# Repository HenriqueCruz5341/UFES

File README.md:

# UFES
Repositório para adicionar os exercícios e projetos que realizo durante minhas matérias que envolvem programação do curso de Engenharia de Computação, na UFES Campus Goiabeiras.

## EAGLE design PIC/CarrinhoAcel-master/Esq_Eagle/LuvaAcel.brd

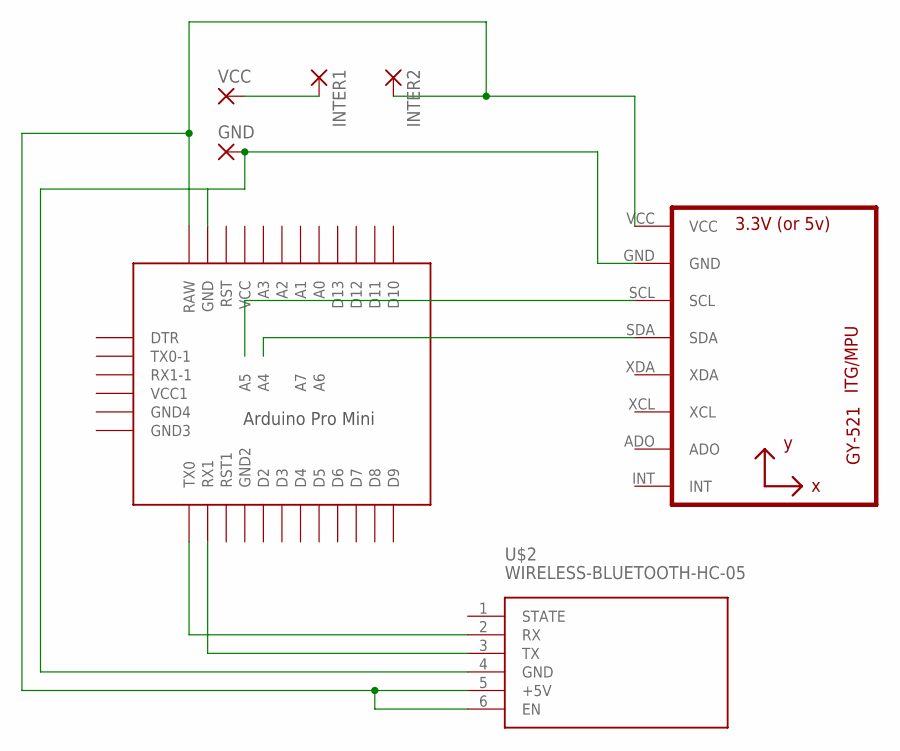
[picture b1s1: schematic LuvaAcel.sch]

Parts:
GND: 3,17/1,1
INTER1, INTER2: 3,17/1,1
U1: GY-521MPU6050; GY-521
U$1: PRO-MINI-2
U$2: WIRELESS-BLUETOOTH-HC-05
VCC: 3,17/1,1

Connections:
unnamed: U1.SCL, U$1.A5
unnamed: U1.SDA, U$1.A4
unnamed: GND.1, U1.GND, U$1.GND, U$2.4 (GND)
unnamed: U$1.TX0, U$2.2 (RX)
unnamed: U$1.RX1, U$2.3 (TX)
unnamed: INTER2.1, U1.VCC, U$1.RAW, U$2.5 (+5V), U$2.6 (EN)
unnamed: INTER1.1, VCC.1

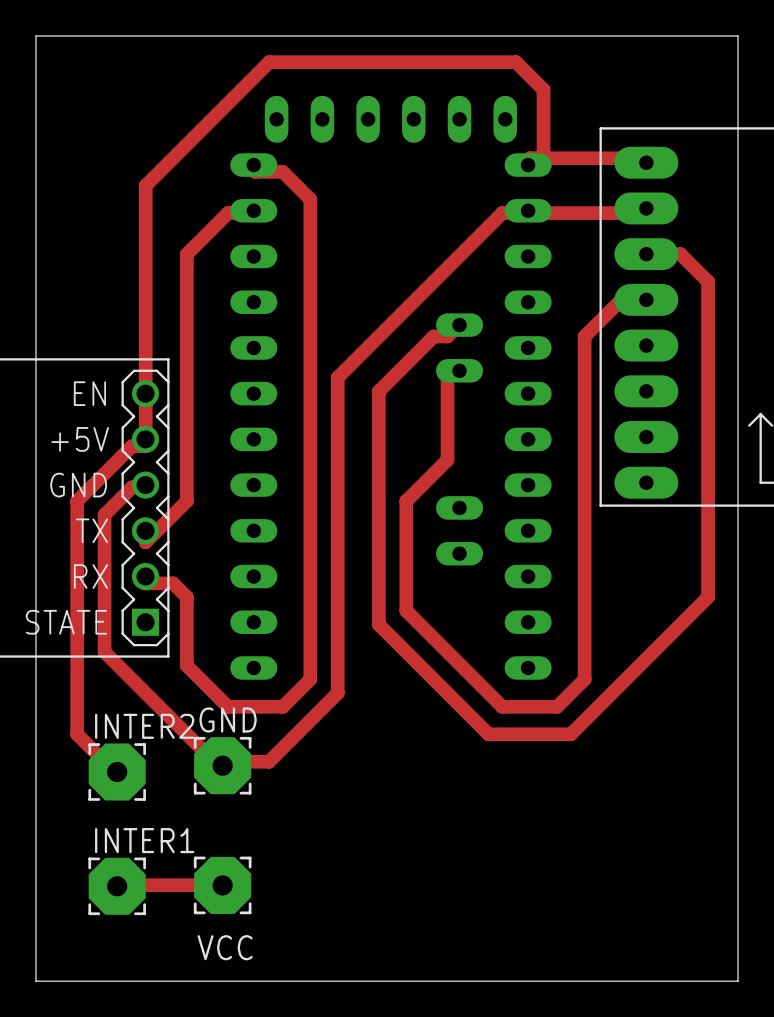
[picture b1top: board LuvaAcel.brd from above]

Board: 2 copper layers, 39.0 x 52.5 mm, 7 parts (0 on the bottom side), 7 nets.

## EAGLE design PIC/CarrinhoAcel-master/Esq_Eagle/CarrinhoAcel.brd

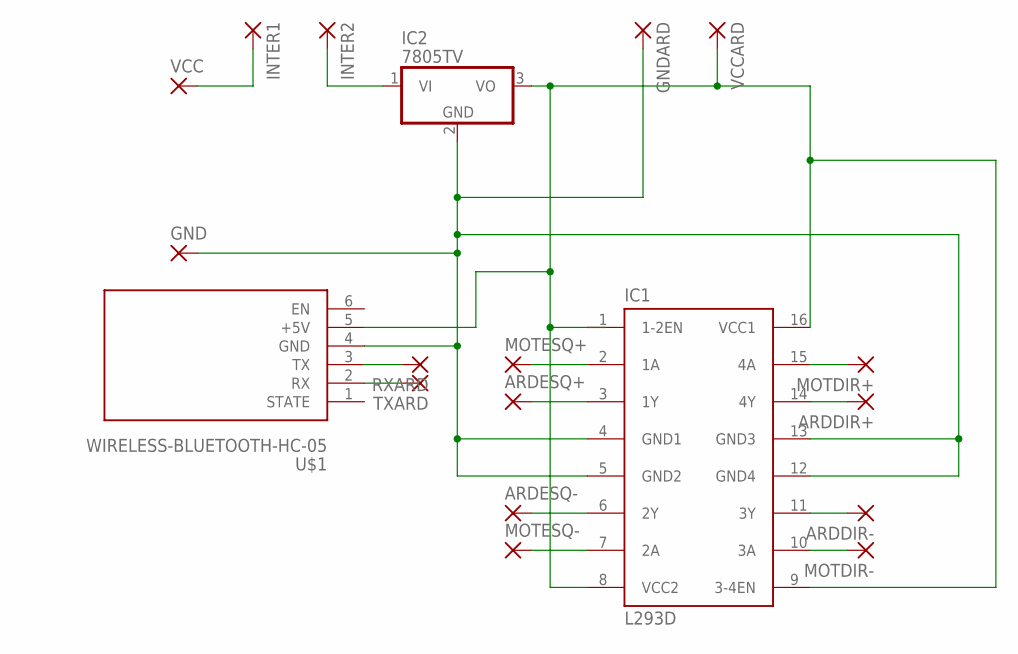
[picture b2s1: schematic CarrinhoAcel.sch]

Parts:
ARDDIR+: 2,15/1,0
ARDDIR-: 2,15/1,0
ARDESQ+: 2,15/1,0
ARDESQ-: 2,15/1,0
GND: 2,15/1,0
GNDARD: 2,15/1,0
IC1: L293D; DIL16
IC2: 7805TV; TO220V
INTER1, INTER2: 2,15/1,0
MOTDIR+: 2,15/1,0
MOTDIR-: 2,15/1,0
MOTESQ+: 2,15/1,0
MOTESQ-: 2,15/1,0
RXARD: 2,15/1,0
TXARD: 2,15/1,0
U$1: WIRELESS-BLUETOOTH-HC-05
VCC: 2,15/1,0
VCCARD: 2,15/1,0

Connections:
unnamed: INTER1.1, VCC.1
unnamed: GND.1, GNDARD.1, IC1.4 (GND1), IC1.5 (GND2), IC1.12 (GND4), IC1.13 (GND3), IC2.2 (GND), U$1.4 (GND)
unnamed: IC1.2 (1A), MOTESQ+.1
unnamed: ARDESQ+.1, IC1.3 (1Y)
unnamed: ARDESQ-.1, IC1.6 (2Y)
unnamed: IC1.7 (2A), MOTESQ-.1
unnamed: IC1.1 (1-2EN), IC1.8 (VCC2), IC1.9 (3-4EN), IC1.16 (VCC1), IC2.3 (VO), U$1.5 (+5V), VCCARD.1
unnamed: IC1.10 (3A), MOTDIR-.1
unnamed: ARDDIR-.1, IC1.11 (3Y)
unnamed: ARDDIR+.1, IC1.14 (4Y)
unnamed: IC1.15 (4A), MOTDIR+.1
unnamed: RXARD.1, U$1.3 (TX)
unnamed: IC2.1 (VI), INTER2.1
unnamed: TXARD.1, U$1.2 (RX)

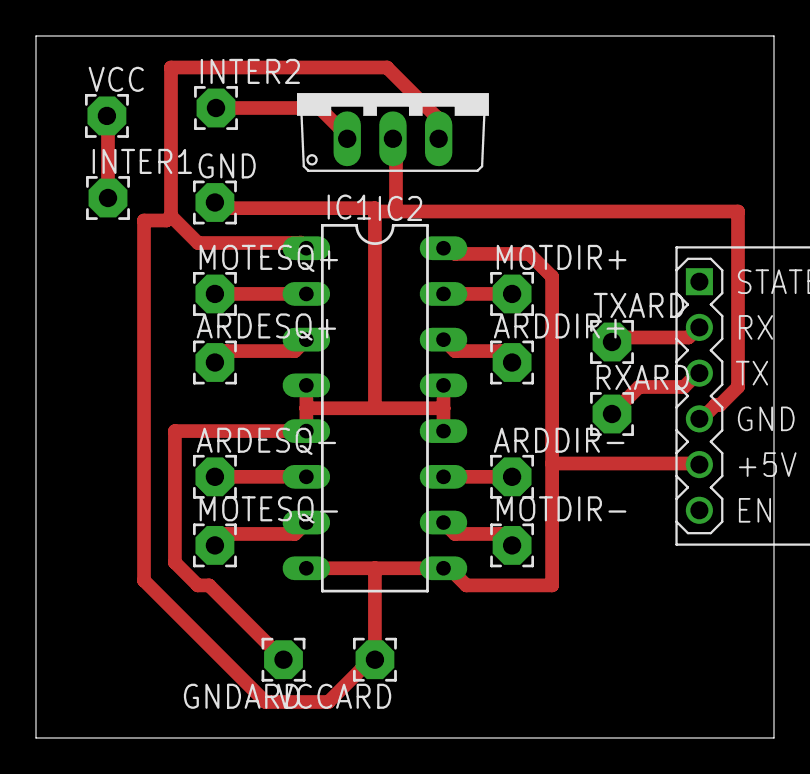
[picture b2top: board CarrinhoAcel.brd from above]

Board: 2 copper layers, 41.0 x 39.0 mm, 19 parts (0 on the bottom side), 14 nets.

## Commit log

2019-09-17 Adicionando o .gitignore para PDF
2019-09-17 Adicionando exercicios de TEP_I e PROG_II
2019-09-17 Removi o arquivo Jogo.zip da pasta Prog_II
2019-09-26 Adicionando mais exercicios e PIC
2019-09-26 Adicionando mais exercicios
2019-10-03 Adicionando BigInt_06
2019-10-04 Adicionando exercicio BigInt_05
2019-10-09 Adicionando exercicio do acelerometro completo
2019-10-17 Adicionando exercicio e Ponto
2019-10-22 Adicionando TAD circulo
2019-10-29 Atualizando o projeto Ponto
2019-10-29 Exemplo de makefile e TAD matriz
2019-10-31 Update 31/10
2019-10-31 comecando trabalho
2019-11-05 Nao alterei nada
2019-11-06 modificacoes no trabalho0
2019-11-07 alteracoes no trabalho
2019-11-07 mudancas trabalho ufes
2019-11-07 Concertando
2019-11-07 funcionando algumas edicoes
2019-11-11 atualizacao trabalho
2019-11-12 Comecando a mexer com usuarios
2019-11-13 melhorando usuarios
2019-11-14 melhorando trabalho
2019-11-17 Comecando a implementar playlists
2019-11-19 Terminei playlists
2019-11-19 Comecando a implementar sistema
2019-11-20 avancei na parte de usuarios publicos e admin
2019-11-21 Terminei o bruto
2019-11-21 Concertando erros
2019-11-21 Aparentemente, ta pronto
2019-11-26 Atualiacoes
2019-11-26 Comecando a documentacao
2019-11-27 continuando a documentacao
2019-11-28 Atualizando
2019-11-28 Terminei de comentar a main
2019-11-29 terminando comentarios da main
2019-12-01 Terminei a documentacao
2019-12-07 Colocando o PDF
2019-12-10 colocando o programa em estagio padrao
2019-12-11 colocando arquivos do curso de JS
2019-12-18 Adicionando cursoJS
2020-01-06 criando singlePage
2020-01-07 adicionando um Exemplo de integração entre React e Bootstrap
2020-02-05 Curso Omnistack
2020-02-26 Melhorando teste da JACEE
2020-02-27 Melhorando site JACEE
2020-03-15 adicionando ED1
2020-03-18 Adicionando exercicio da aula2 de ED1
2020-04-09 Adicionando exercicios da Aula3 de ED1
2020-04-22 Adicionando a pasta web do PET para backup
2020-04-22 Bump minimist from 1.2.0 to 1.2.5 in /web/jacee/backend
    Bumps [minimist](https://github.com/substack/minimist) from 1.2.0 to 1.2.5.
    - [Release notes](https://github.com/substack/minimist/releases)
    - [Commits](https://github.com/substack/minimist/compare/1.2.0...1.2.5)
2020-04-23 fazendo alterações no multerConfig
2020-04-30 Adicionando outros exercícios de ED1 e excluindo projetos
2020-05-04 Adicionando a parte de noticias
2020-07-07 removendo node_modules e adicionando aula4 de ED
2020-08-07 Bump minimist in /CursoJavaScript/semanaOmniStack/backend
    Bumps [minimist](https://github.com/substack/minimist) from 1.2.0 to 1.2.5.
    - [Release notes](https://github.com/substack/minimist/releases)
    - [Commits](https://github.com/substack/minimist/compare/1.2.0...1.2.5)
2020-08-20 Adcionando ListaHeteronegena ED1
2020-09-03 Bump bl from 2.2.0 to 2.2.1 in /web/sitePet/backend
    Bumps [bl](https://github.com/rvagg/bl) from 2.2.0 to 2.2.1.
    - [Release notes](https://github.com/rvagg/bl/releases)
    - [Commits](https://github.com/rvagg/bl/compare/v2.2.0...v2.2.1)
2020-09-13 Bump node-fetch from 2.6.0 to 2.6.1 in /web/sitePet/backend
    Bumps [node-fetch](https://github.com/bitinn/node-fetch) from 2.6.0 to 2.6.1.
    - [Release notes](https://github.com/bitinn/node-fetch/releases)
    - [Changelog](https://github.com/node-fetch/node-fetch/blob/master/docs/CHANGELOG.md)
    - [Commits](https://github.com/bitinn/node-fetch/compare/v2.6.0...v2.6.1)
2020-10-29 Adicionando novos exercícios de ED1
2020-11-03 Começando trabalho de ED1
2020-11-18 Adicionando trabalho1 de ED1
2020-11-18 Bump dot-prop in /CursoJavaScript/semanaOmniStack/backend
    Bumps [dot-prop](https://github.com/sindresorhus/dot-prop) from 4.2.0 to 4.2.1.
    - [Release notes](https://github.com/sindresorhus/dot-prop/releases)
    - [Commits](https://github.com/sindresorhus/dot-prop/compare/v4.2.0...v4.2.1)
2020-11-20 Trabalho pronto, falta comentar
2020-12-08 Adicionando alguns exercicios e o trabalho1 de EDI
2020-12-09 Adicionando Exercicio11
2020-12-13 Bump ini from 1.3.5 to 1.3.8 in /CursoJavaScript/semanaOmniStack/backend
    Bumps [ini](https://github.com/isaacs/ini) from 1.3.5 to 1.3.8.
    - [Release notes](https://github.com/isaacs/ini/releases)
    - [Commits](https://github.com/isaacs/ini/compare/v1.3.5...v1.3.8)
2020-12-13 Bump ini from 1.3.5 to 1.3.8 in /web/sitePet/backend
    Bumps [ini](https://github.com/isaacs/ini) from 1.3.5 to 1.3.8.
    - [Release notes](https://github.com/isaacs/ini/releases)
    - [Commits](https://github.com/isaacs/ini/compare/v1.3.5...v1.3.8)
2021-01-06 Bump axios in /CursoJavaScript/semanaOmniStack/backend
    Bumps [axios](https://github.com/axios/axios) from 0.19.1 to 0.21.1.
    - [Release notes](https://github.com/axios/axios/releases)
    - [Changelog](https://github.com/axios/axios/blob/v0.21.1/CHANGELOG.md)
    - [Commits](https://github.com/axios/axios/compare/0.19.1...v0.21.1)
2021-02-03 Adicionando Exercicio12 e o Trabalho2 de ED1
2021-02-03 Removendo 'web' e 'CursoJavaScript' para organizar o repositório
2021-02-06 Criando ED2, e adicionando os códigos da segunda aula
2021-02-08 Renomeando pastas para o padrao
2021-02-12 Enviando atividades de ED2 e Prog3
2021-02-17 Adicionando o Lab1 de ED2
2021-02-20 adicionando lab2 de ED2
2021-02-22 removendo modificador public
2021-02-25 Adicionando Lab3 de ED2
2021-02-25 Adicionando modo configuração para depurar em C no vscode
2021-02-25 Adicionando exercicios da aula05
2021-03-26 Adicionando lab4 de ED2
2021-03-26 Adicionando exercicios da aula 10 de Prog3
2021-03-27 Adicionando o lab5 de ED2
2021-04-19 Adicionando TrabalhoJAVA
2021-06-14 enviando trabalhoC++
2021-06-14 removendo arquivos de entrada e saida
2021-07-17 exercicios de programacao competitiva
2021-08-12 adicionando aula10 de p1 de ProgComp
2021-09-22 add more exercises
2022-05-08 criei um novo arquivo para ensinar git
2022-05-08 coloquei uma soma
2022-05-08 corrigindo
2022-05-08 alterei
2022-05-08 removendo pasta para ensinar git para um amigo
2022-07-19 iniciando com freertr

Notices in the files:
parts and their libraries:
diy-modules: Released under the Creative Commons Attribution 4.0 International License: http://creativecommons.org/licenses/by/4.0
